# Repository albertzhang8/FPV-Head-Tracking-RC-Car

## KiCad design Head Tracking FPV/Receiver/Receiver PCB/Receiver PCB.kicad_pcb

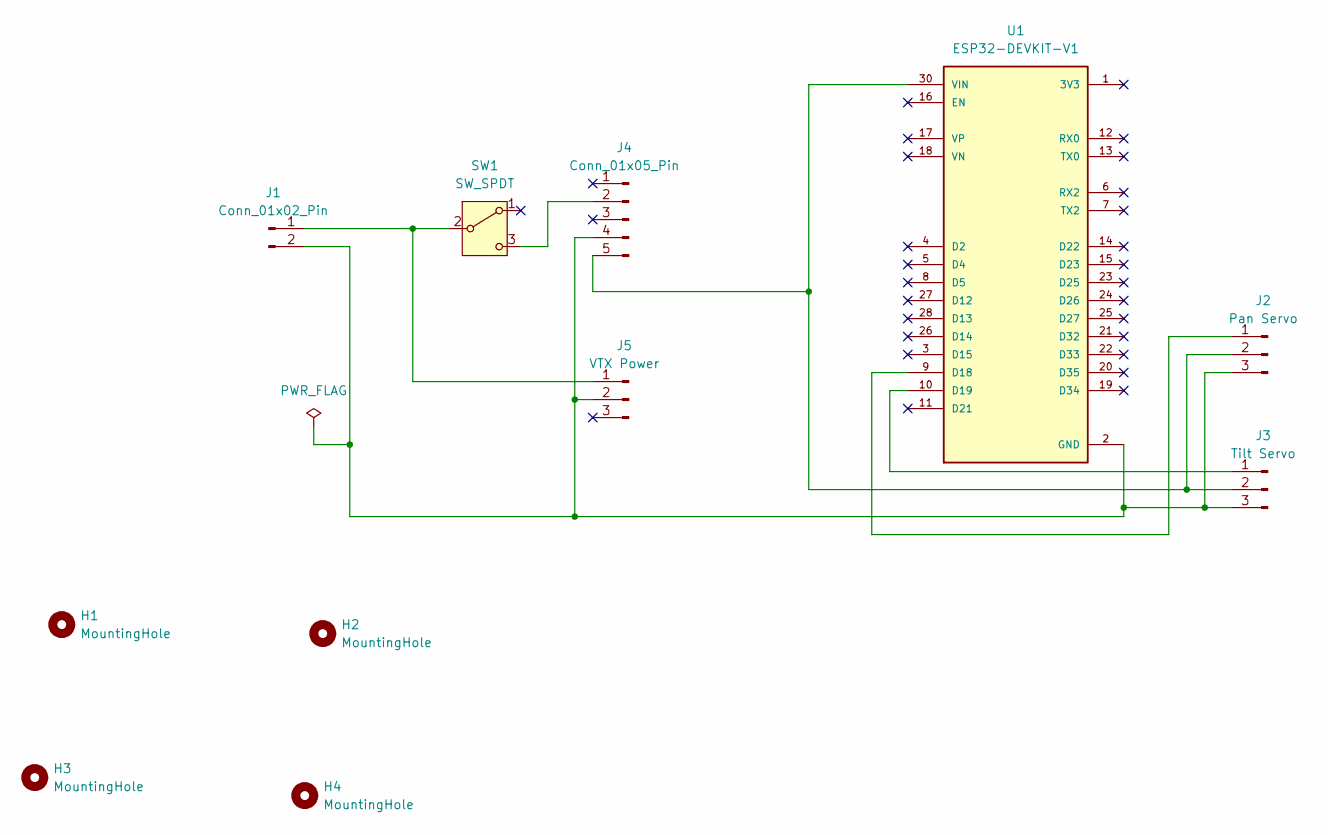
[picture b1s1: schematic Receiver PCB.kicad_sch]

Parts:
H1, H2, H3, H4: MountingHole; MountingHole_3.2mm_M3
J1: Conn_01x02_Pin; JST_PH_B2B-PH-K_1x02_P2.00mm_Vertical
J2: Pan Servo; PinHeader_1x03_P2.54mm_Vertical
J3: Tilt Servo; PinHeader_1x03_P2.54mm_Vertical
J4: Conn_01x05_Pin; PinHeader_1x05_P2.54mm_Vertical
J5: VTX Power; 3_Pin_SMD_Header_Custom
SW1: SW_SPDT; SW_EG1218
U1: ESP32-DEVKIT-V1; MODULE_ESP32_DEVKIT_V1; PARTREV N/A

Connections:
GND: J1.2, J2.3, J3.3, J4.4, J5.2, U1.2 (GND), U1.29 (GND)
unnamed: J1.1, J5.1, SW1.2 (B)
unnamed: J2.1, U1.9 (D18)
unnamed: J2.2, J3.2, J4.5, U1.30 (VIN)
unnamed: J3.1, U1.10 (D19)
unnamed: J4.2, SW1.3 (C)

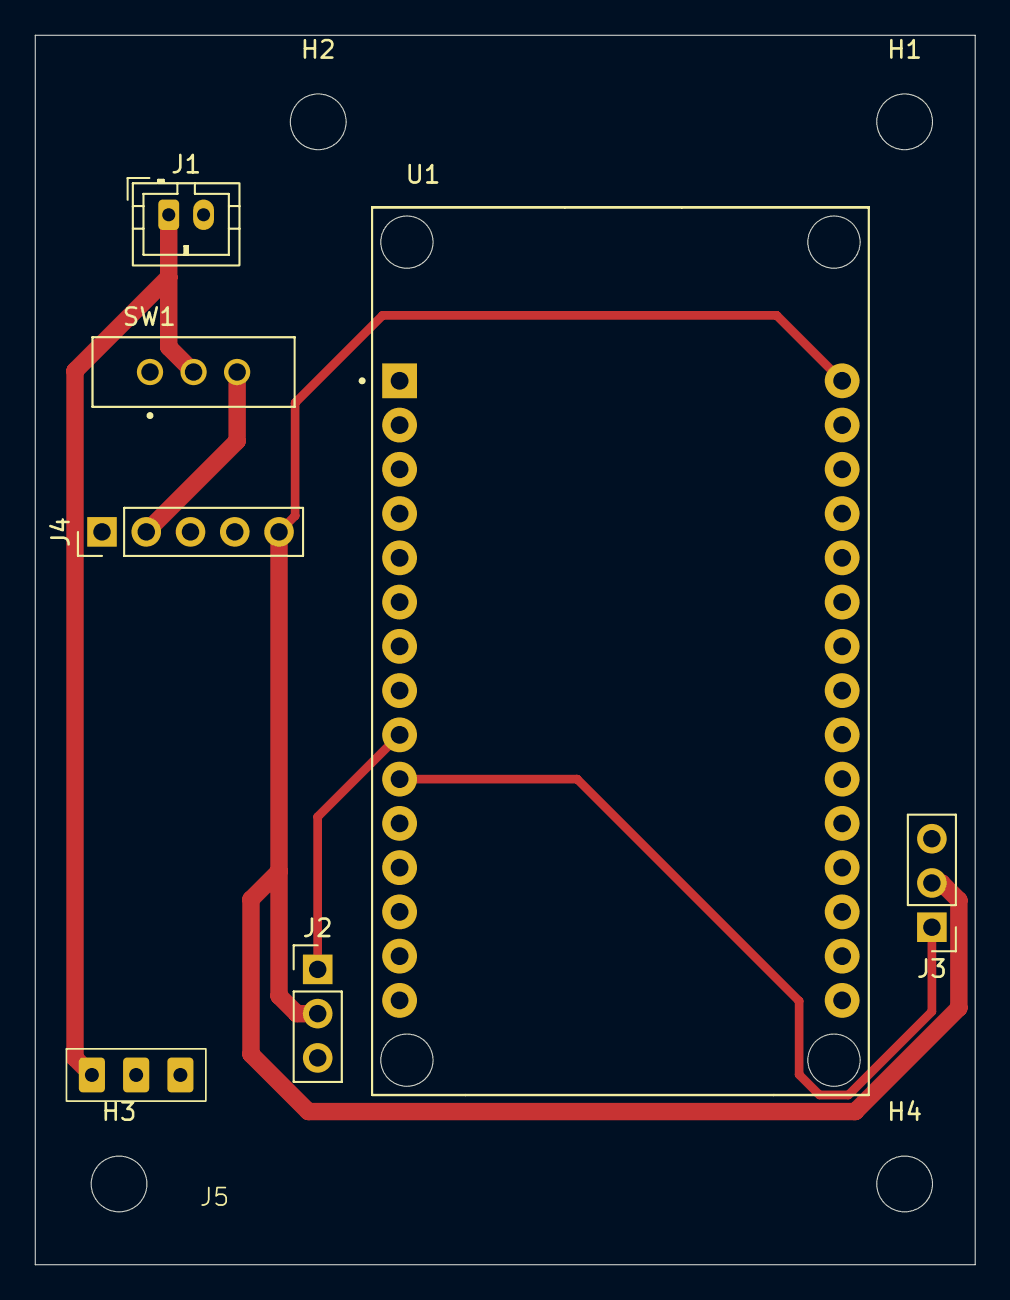
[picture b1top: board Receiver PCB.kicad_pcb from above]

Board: 2 copper layers, 53.9 x 70.6 mm, 11 parts (0 on the bottom side), 6 nets.

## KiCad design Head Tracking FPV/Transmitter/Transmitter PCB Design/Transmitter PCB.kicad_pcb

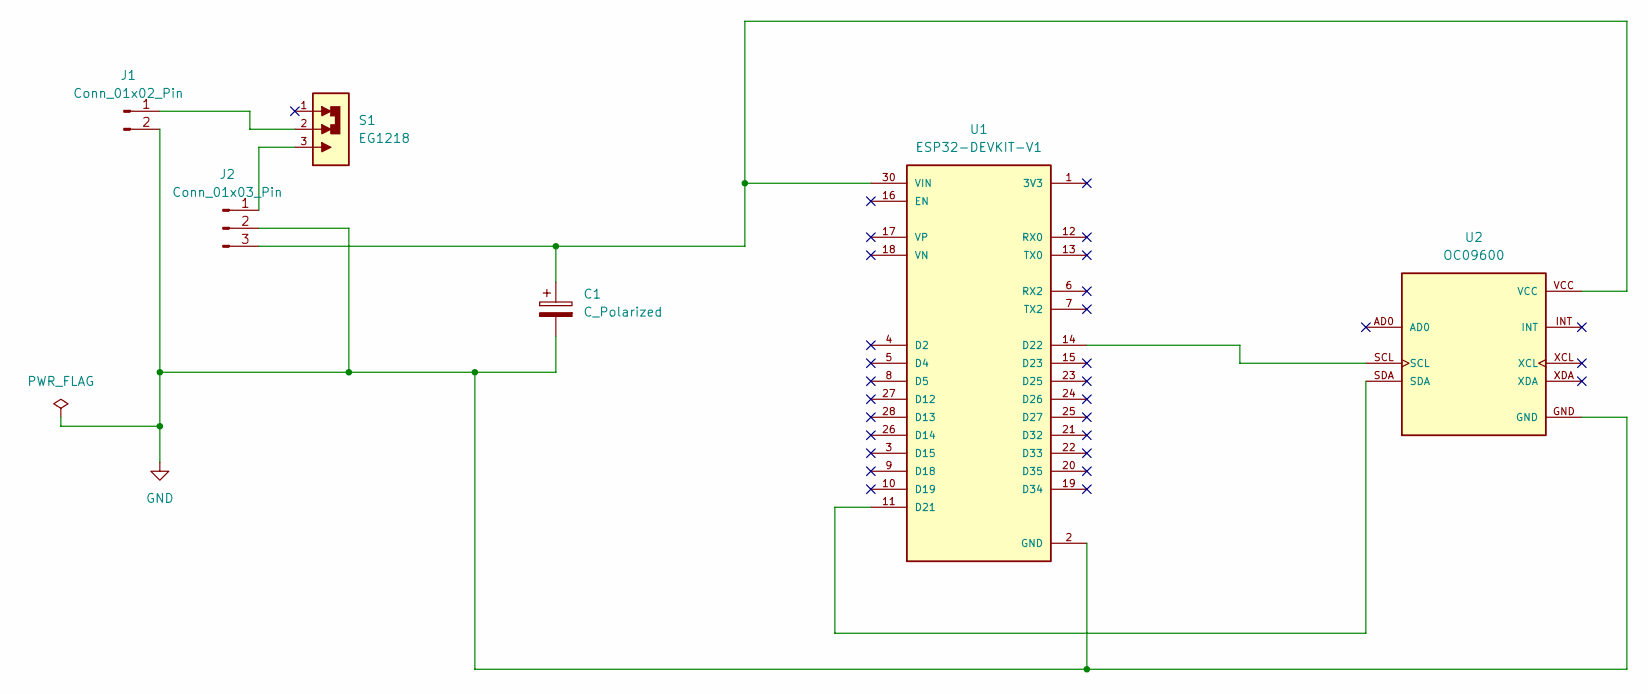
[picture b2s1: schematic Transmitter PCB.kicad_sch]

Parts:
C1: C_Polarized; CP_Radial_D5.0mm_P2.00mm
J1: Conn_01x02_Pin; JST_PH_S2B-PH-K_1x02_P2.00mm_Horizontal
J2: Conn_01x03_Pin; PinHeader_1x03_P2.54mm_Vertical
S1: EG1218; SW_EG1218
U1: ESP32-DEVKIT-V1; MODULE_ESP32_DEVKIT_V1; PARTREV N/A
U2: OC09600; MODULE_OC09600; PARTREV NA

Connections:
GND: C1.2, J1.2, J2.2, U1.2 (GND), U1.29 (GND), U2.GND
unnamed: J1.1, S1.2
unnamed: J2.1, S1.3
unnamed: C1.1, J2.3, U1.30 (VIN), U2.VCC
unnamed: U1.11 (D21), U2.SDA
unnamed: U1.14 (D22), U2.SCL

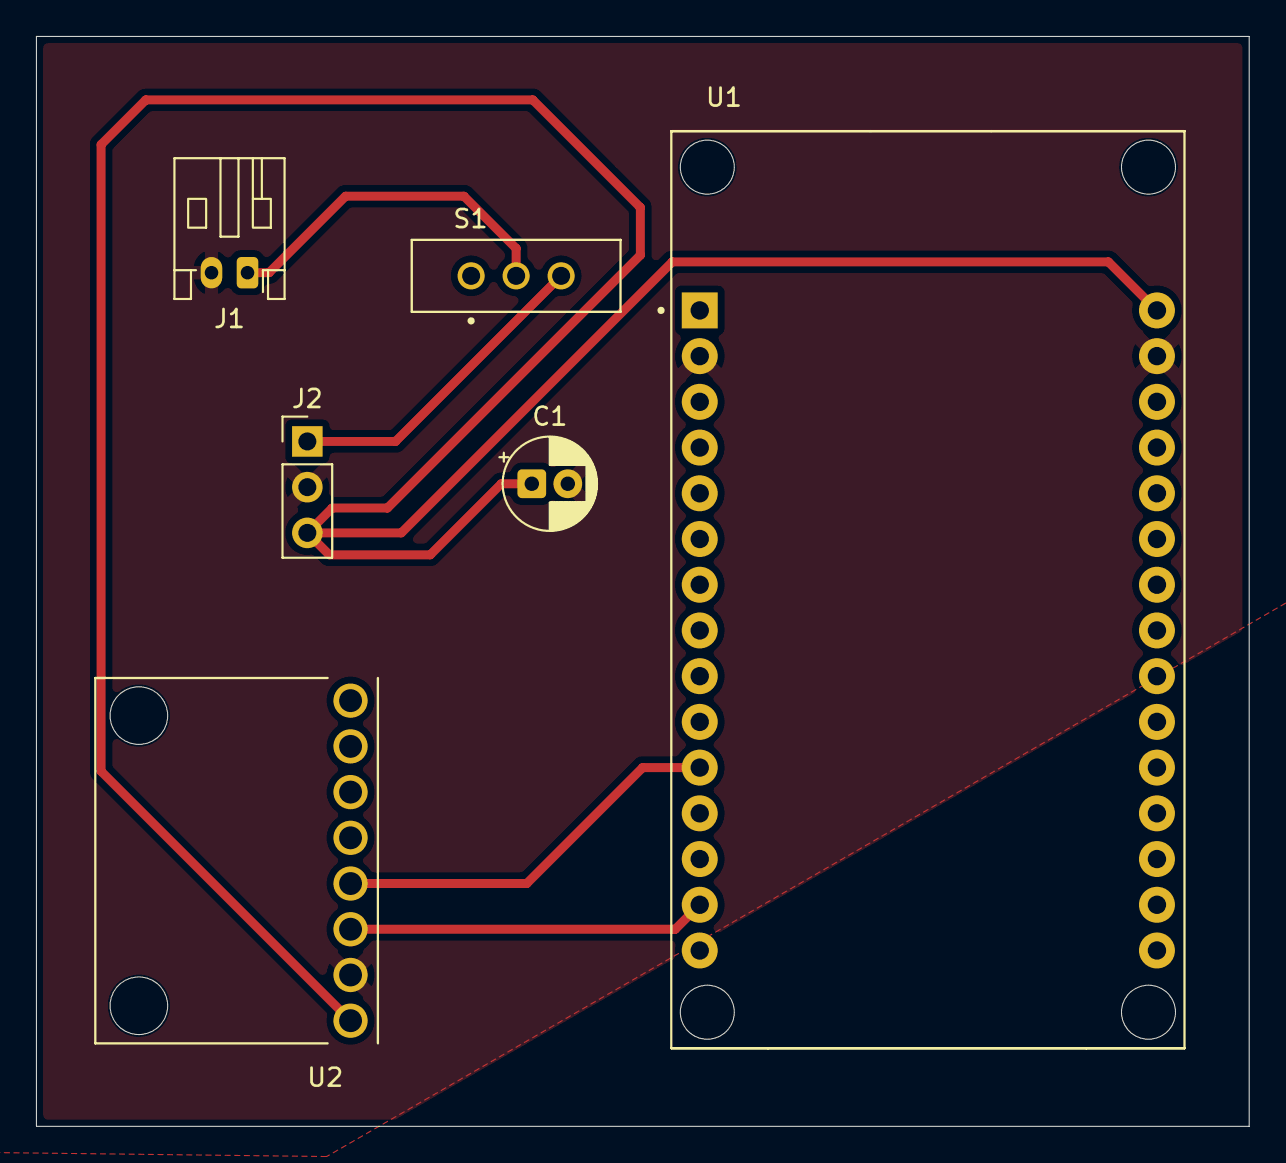
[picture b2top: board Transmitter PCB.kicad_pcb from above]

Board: 2 copper layers, 67.4 x 60.6 mm, 6 parts (0 on the bottom side), 6 nets.

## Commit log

2026-06-16 Inputting STLs for front assembly + Adding folders
2026-06-18 Finished Transmitter PCB
2026-06-19 Done With Receiver PCB
2026-06-20 Added STLs for steering
2026-06-21 Finished Assembly
2026-06-21 New Assembly
2026-06-21 Created gerber files for receiver
2026-06-22 Added Mounting Holes
